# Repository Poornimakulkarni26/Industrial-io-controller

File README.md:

# Industrial IO Controller

A general-purpose industrial I/O controller board built around the **RP2040** microcontroller. Designed for rapid prototyping, hardware validation, and testing across a wide range of sensors, actuators, and communication protocols — all from a single PCB.

## Board Preview

## Features

### Digital I/O
- **20+ configurable digital inputs** — connect buttons, proximity sensors, limit switches, photoelectric sensors, or any industrial-standard digital signal
- **20+ configurable digital outputs** — drive stepper motors, solenoid valves, relays, indicators, and more

### Analog
- **Multi-channel ADC inputs** — for vacuum sensors, pressure transducers, temperature probes, or any 0–3.3V analog signal
- **Current sensing channels** — monitor current draw and detect spikes for motor protection or diagnostics

### Lighting
- **NeoPixel (WS2812B) output** — addressable RGB LED support for status indication, tower lights, or visual feedback

### Storage
- **FRAM (Ferroelectric RAM)** — non-volatile, high-endurance storage for configuration data, counters, or logs that survive power cycles without wear concerns

### Communication Protocols
Designed to test and validate nearly every common protocol from a single board:
- **SPI**
- **I2C**
- **UART**
- **And more** — exposed headers and test points for easy hookup

## Specifications

| Parameter | Value |
|---|---|
| Microcontroller | RP2040 (Dual-core Arm Cortex-M0+, 133 MHz) |
| Digital Inputs | 20+ channels |
| Digital Outputs | 20+ channels |
| Analog Inputs | Multi-channel ADC |
| Current Sensing | Dedicated channels |
| LED Output | NeoPixel (WS2812B) compatible |
| Non-volatile Storage | FRAM |
| Communication | SPI, I2C, UART |
| EDA Tool | KiCad |

## Getting Started

### Viewing the Design
1. Install [KiCad](https://www.kicad.org/) (v7+ recommended)
2. Clone this repository:
   ```bash
   git clone https://github.com/Poornimakulkarni26/Industrial-io-controller.git
   ```
3. Open the `.kicad_pro` project file in KiCad

### Ordering the Board
1. Export Gerber files from KiCad (**File → Fabrication Outputs → Gerbers**)
2. Upload to your preferred PCB manufacturer (JLCPCB, PCBWay etc.)

## Design Highlights

- **Industrial-grade I/O count** — enough channels to prototype full machine control without daisy-chaining expanders
- **Protocol-agnostic test platform** — validate SPI, I2C, UART peripherals without rewiring
- **Mixed-signal capability** — digital I/O, analog sensing, and current monitoring on one board
- **NeoPixel integration** — visual feedback built in, no separate LED driver board needed
- **FRAM over EEPROM** — virtually unlimited write cycles for high-frequency data logging

## Use Cases

- Sensor and actuator validation benches
- Stepper motor driver testing
- Communication protocol bring-up and debugging
- Industrial automation prototyping
- Embedded firmware development and testing

## Author

**Poornima Kulkarni**
Embedded Systems & Industrial Automation Engineer

- GitHub: [@Poornimakulkarni26](https://github.com/Poornimakulkarni26)
https://www.linkedin.com/in/poornima-kulkarni-35ba682a3?utm_source=share_via&utm_content=profile&utm_medium=member_android

## License
This project is open-source under the [MIT License](LICENSE).

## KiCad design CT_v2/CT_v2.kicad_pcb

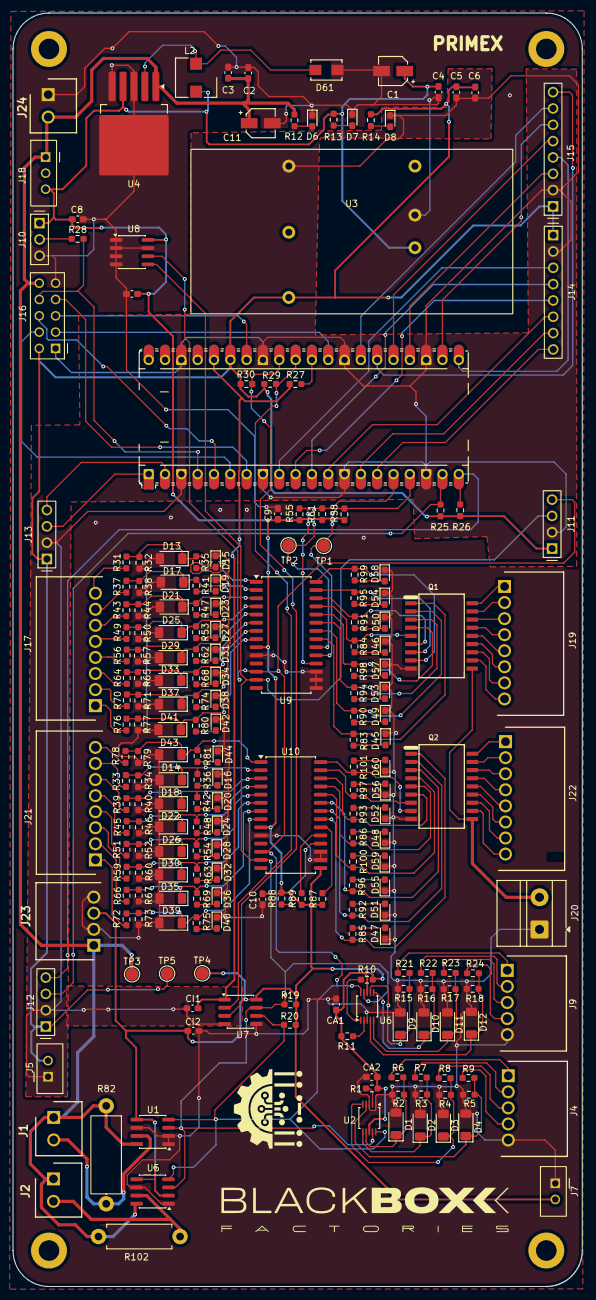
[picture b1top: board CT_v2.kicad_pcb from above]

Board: 4 copper layers, 88.6 x 198.2 mm, 221 parts (0 on the bottom side), 162 nets.

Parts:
100nF3: C_Small; C_0603_1608Metric_Pad1.08x0.95mm_HandSolder
A1: RaspberryPi_Pico; RaspberryPi_Pico_Common_Unspecified
C1: D4L5.5_865060140002; CP_Wurth_WCAP-ASLL-D4L5.5
C2, C4: 100nF; C_0603_1608Metric_Pad1.08x0.95mm_HandSolder
C3: 10pF; C_0603_1608Metric_Pad1.08x0.95mm_HandSolder
C5, C9, C10: 1uF; C_0603_1608Metric_Pad1.08x0.95mm_HandSolder
C6: 10uF; C_0603_1608Metric_Pad1.08x0.95mm_HandSolder
C8: 0.1uF; C_0603_1608Metric_Pad1.08x0.95mm_HandSolder
C11: D4L5.5_865060340001; CP_Wurth_WCAP-ASLL-D4L5.5
CA1, CA2: C_Small; C_0603_1608Metric_Pad1.08x0.95mm_HandSolder
CI1, CI2: C_Small; C_0603_1608Metric_Pad1.08x0.95mm_HandSolder
D1, D2, D3, D4, D9, D10, D11, D12, D13, D14, D17, D18, D21, D22, D25, D26, D29, D30, D33, D35, D37, D39, D41, D43: BZV55C51; D_MiniMELF
D6, D7, D8, D15, D16, D19, D20, D23, D24, D27, D28, D31, D32, D34, D36, D38, D40, D42, D44, D45, D46, D47, D48, D49, D50, D51, D52, D53, D54, D55, D56, D57, D58, D59, D60: LED; LED_0603_1608Metric_Pad1.05x0.95mm_HandSolder
D61: M7; M7_DIO
H1, H2, H3, H4: MountingHole; MountingHole_3.2mm_M3_DIN965_Pad
J1, J2, J24: 691321100002; SHDR2W80P0X350_1X2_840X720X920P
J4, J9: 691382010005; SHDRRA5W80P0X250_1X5_1450X1010X830P
J5, J7: 68800211622; J_Wurth_WR-WTB_68800211622
J10: 61300311121; J_Wurth_WR-PHD_61300311121
J11, J12, J13: 61000418221; J_Wurth_WR-PHD_61300411121
J14, J15: 61000821121; J_Wurth_WR-PHD_61300811121
J16: 61301021821; J_Wurth_WR-PHD_61301021821
J17, J19, J21, J22: 691382010008; SHDRRA8W80P0X250_1X8_2200X1010X830P
J18: 68800311622; J_Wurth_WR-WTB_68800311622
J20: Screw_Terminal_01x02; TerminalBlock_MetzConnect_Type011_RT05502HBLC_1x02_P5.00mm_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
J23: 691382010004; SHDRRA4W80P0X250_1X4_1200X1010X810P
L2: 6033R_744778520; L_Wurth_WE-PD-6033R
Q1, Q2: TBD62083AFG_EL; SOIC127P1030X245-18N
R1, R19, R20, R25, R26, R27, R29, R30, R55, R58, R61, R87, R88, R89: 10k; R_0603_1608Metric_Pad0.98x0.95mm_HandSolder
R2, R3, R4, R5, R15, R16, R17, R18, R32, R34, R38, R40, R44, R46, R50, R52, R57, R60, R65, R67, R71, R73, R77, R79: 1k; R_0603_1608Metric_Pad0.98x0.95mm_HandSolder
R6, R7, R8, R9, R21, R22, R23, R24: 2k; R_0603_1608Metric_Pad0.98x0.95mm_HandSolder
R10, R11: 10K; R_0603_1608Metric_Pad0.98x0.95mm_HandSolder
R12, R13, R14: 1.2k; R_0603_1608Metric_Pad0.98x0.95mm_HandSolder
R28: 470; R_0603_1608Metric_Pad0.98x0.95mm_HandSolder
R31, R33, R37, R39, R43, R45, R49, R51, R56, R59, R64, R66, R70, R72, R76, R78: 3.9k; R_0603_1608Metric_Pad0.98x0.95mm_HandSolder
R35, R36, R41, R42, R47, R48, R53, R54, R62, R63, R68, R69, R74, R75, R80, R81, R83, R84, R85, R86, R90, R91, R92, R93, R94, R95, R96, R97, R98, R99, R100, R101: 330; R_0603_1608Metric_Pad0.98x0.95mm_HandSolder
R82: 0.1; R_Axial_DIN0414_L11.9mm_D4.5mm_P15.24mm_Horizontal
R102: 0.1; R_Axial_DIN0411_L9.9mm_D3.6mm_P12.70mm_Horizontal
TP1, TP2, TP3, TP4, TP5: TestPoint; TestPoint_Pad_D2.0mm
U1, U5: INA219AxD; SOIC-8_3.9x4.9mm_P1.27mm
U2, U6: ADS1115IDGS; TSSOP-10_3x3mm_P0.5mm
U3: ECB4U-05S03; Ec4ub-24s05
U4: LM2576HVS-5; TO-263-5_TabPin3
U7: ISO1540; SOIC-8_3.9x4.9mm_P1.27mm
U8: FM24C64B; SOIC-8_3.9x4.9mm_P1.27mm
U9: IN_MCP23017; SOIC-28W_7.5x17.9mm_P1.27mm
U10: MCP23017_SO; SOIC-28W_7.5x17.9mm_P1.27mm

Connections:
+3.3V: A1.35 (ADC_VREF), C5.1, C6.1, J5.2, J11.1, J12.1, J13.1, J14.1, J15.1, J16.2, R14.1, R25.1, R26.2, R29.1, R30.2, TP5.1, U3.3 (+V)
+5V: 100nF3.1, C1.1, C4.1, C8.1, C9.1, C10.1, CA1.1, CA2.1, CI2.2, J7.2, J10.1, J18.3, J23.3, L2.2, R1.1, R10.1, R11.1, R13.1, R19.1, R20.2, R55.2, R58.1, R61.1, R87.1, R88.2, R89.1, TP4.1, U1.5 (VS), U2.8 (VDD), U3.1 (IN+), U4.4 (FB), U5.2 (A0), U5.5 (VS), U6.8 (VDD), U7.8 (VCC2), U8.8 (VDD), U9.9 (VDD), U10.9 (VDD), U10.15 (A0)
+24V: C2.1, C3.1, C11.1, J1.1, J2.1, J16.10, J18.1, J23.1, J24.2, R12.1, R82.1, R102.1, TP3.1, U1.8 (IN+), U4.1 (VIN), U5.8 (IN+)
+ 3.3V: A1.36 (3V3), CI1.1, R27.1, U7.1 (VCC1)
-24VA: J1.2, R82.2, U1.7 (IN-)
-24VB: J2.2, R102.2, U5.7 (IN-)
ADC2: A1.34 (GPIO28_ADC2), J16.5
CS1: A1.12 (GPIO9), J14.6
CS2: A1.14 (GPIO10), J14.7
CS3: A1.15 (GPIO11), J14.8
Din: A1.4 (GPIO2), J16.8, R28.2
GND: 100nF3.2, C1.2, C2.2, C3.2, C4.2, C8.2, C9.2, C10.2, C11.2, CA1.2, CA2.2, CI2.1, D1.2 (A), D2.2 (A), D3.2 (A), D4.2 (A), D6.1 (K), D7.1 (K), D9.2 (A), D10.2 (A), D11.2 (A), D12.2 (A), D13.2 (A), D14.2 (A), D15.1 (K), D16.1 (K), D17.2 (A), D18.2 (A), D19.1 (K), D20.1 (K), D21.2 (A), D22.2 (A), D23.1 (K), D24.1 (K), D25.2 (A), D26.2 (A), D27.1 (K), D28.1 (K), D29.2 (A), D30.2 (A), D31.1 (K), D32.1 (K), D33.2 (A), D34.1 (K), D35.2 (A), D36.1 (K), D37.2 (A), D38.1 (K), D39.2 (A), D40.1 (K), D41.2 (A), D42.1 (K), D43.2 (A), D44.1 (K), D45.1 (K), D46.1 (K), D47.1 (K), D48.1 (K), D49.1 (K), D50.1 (K), D51.1 (K), D52.1 (K), D53.1 (K), D54.1 (K), D55.1 (K), D56.1 (K), D57.1 (K), D58.1 (K), D59.1 (K), D60.1 (K), D61.1, J4.5, J7.1, J9.5, J10.3, J16.9, J20.1, J23.2, J23.4, J24.1, Q1.9 (GND), Q2.9 (GND), R2.2, R3.2, R4.2, R5.2, R15.2, R16.2, R17.2, R18.2, R32.2, R34.2, R38.2, R40.2, R44.2, R46.2, R50.2, R52.2, R57.2, R60.2, R65.2, R67.2, R71.2, R73.2, R77.2, R79.2, U1.1 (A1), U1.2 (A0), U1.6 (GND), U2.1 (ADDR), U2.3 (GND), U3.2 (IN-), U4.3 (GND), U4.5 (~ON/OFF), U5.1 (A1), U5.6 (GND), U6.3 (GND), U7.5 (GND2), U8.1 (A0), U8.2 (A1), U8.3 (A2), U8.4 (VSS), U8.7 (WP), U9.10 (VSS), U9.15 (A0), U9.16 (A1), U9.17 (A2), U10.10 (VSS), U10.16 (A1), U10.17 (A2)
GP3: A1.5 (GPIO3), J16.6
GP4: A1.6 (GPIO4), J16.4
GP5: A1.7 (GPIO5), J16.7
GP22: A1.29 (GPIO22), J16.3
IP1: J17.8, R31.1
IP1M: D13.1 (K), R31.2, R32.1, R35.1, U9.1 (GPB0)
IP2: J17.7, R37.1
IP2M: D17.1 (K), R37.2, R38.1, R41.1, U9.2 (GPB1)
IP3: J17.6, R43.1
IP3M: D21.1 (K), R43.2, R44.1, R47.1, U9.3 (GPB2)
IP4: J17.5, R49.1
IP4M: D25.1 (K), R49.2, R50.1, R53.1, U9.4 (GPB3)
IP5: J17.4, R56.1
IP5M: D29.1 (K), R56.2, R57.1, R62.1, U9.5 (GPB4)
IP6: J17.3, R64.1
IP6M: D33.1 (K), R64.2, R65.1, R68.1, U9.6 (GPB5)
IP7: J17.2, R70.1
IP7M: D37.1 (K), R70.2, R71.1, R74.1, U9.7 (GPB6)
IP8: J17.1, R76.1
IP8M: D41.1 (K), R76.2, R77.1, R80.1, U9.8 (GPB7)
IP9: J21.8, R78.1
IP9M: D43.1 (K), R78.2, R79.1, R81.1, U10.1 (GPB0)
IP10: J21.7, R33.1
IP10M: D14.1 (K), R33.2, R34.1, R36.1, U10.2 (GPB1)
IP11: J21.6, R39.1
IP11M: D18.1 (K), R39.2, R40.1, R42.1, U10.3 (GPB2)
IP12: J21.5, R45.1
IP12M: D22.1 (K), R45.2, R46.1, R48.1, U10.4 (GPB3)
IP13: J21.4, R51.1
IP13M: D26.1 (K), R51.2, R52.1, R54.1, U10.5 (GPB4)
IP14: J21.3, R59.1
IP14M: D30.1 (K), R59.2, R60.1, R63.1, U10.6 (GPB5)
IP15: J21.2, R66.1
IP15M: D35.1 (K), R66.2, R67.1, R69.1, U10.7 (GPB6)
IP16: J21.1, R72.1
IP16M: D39.1 (K), R72.2, R73.1, R75.1, U10.8 (GPB7)
I_GND: A1.3 (GND), A1.8 (GND), A1.13 (GND), A1.18 (GND), A1.23 (GND), A1.28 (GND), A1.33 (AGND), A1.38 (GND), C5.2, C6.2, CI1.2, D8.1 (K), J5.1, J11.2, J12.2, J13.2, J14.2, J15.2, J16.1, U3.5 (-V), U7.4 (GND1)
I_SCL: A1.32 (GPIO27_ADC1), R30.1, U7.3 (SCL1)
I_SDA: A1.31 (GPIO26_ADC0), R29.2, U7.2 (SDA1)
MISO: A1.11 (GPIO8), J14.4
MOSI: A1.10 (GPIO7), J14.5
unnamed: A1.30 (RUN), R27.2
unnamed: D1.1 (K), R2.1, R6.2, U2.7 (AIN3)
unnamed: D2.1 (K), R3.1, R7.2, U2.6 (AIN2)
unnamed: D3.1 (K), R4.1, R8.2, U2.5 (AIN1)
unnamed: D4.1 (K), R5.1, R9.2, U2.4 (AIN0)
unnamed: D6.2 (A), R12.2
unnamed: D7.2 (A), R13.2
unnamed: D8.2 (A), R14.2
unnamed: D9.1 (K), R15.1, R21.2, U6.7 (AIN3)
unnamed: D10.1 (K), R16.1, R22.2, U6.6 (AIN2)
unnamed: D11.1 (K), R17.1, R23.2, U6.5 (AIN1)
unnamed: D12.1 (K), R18.1, R24.2, U6.4 (AIN0)
unnamed: D15.2 (A), R35.2
unnamed: D16.2 (A), R36.2
unnamed: D19.2 (A), R41.2
unnamed: D20.2 (A), R42.2
unnamed: D23.2 (A), R47.2
unnamed: D24.2 (A), R48.2
unnamed: D27.2 (A), R53.2
unnamed: D28.2 (A), R54.2
unnamed: D31.2 (A), R62.2
unnamed: D32.2 (A), R63.2
unnamed: D34.2 (A), R68.2
unnamed: D36.2 (A), R69.2
unnamed: D38.2 (A), R74.2
unnamed: D40.2 (A), R75.2
unnamed: D42.2 (A), R80.2
unnamed: D44.2 (A), R81.2
unnamed: D45.2 (A), R83.2
unnamed: D46.2 (A), R84.2
unnamed: D47.2 (A), R85.2
unnamed: D48.2 (A), R86.2
unnamed: D49.2 (A), R90.2
unnamed: D50.2 (A), R91.2
unnamed: D51.2 (A), R92.2
unnamed: D52.2 (A), R93.2
unnamed: D53.2 (A), R94.2
unnamed: D54.2 (A), R95.2
unnamed: D55.2 (A), R96.2
unnamed: D56.2 (A), R97.2
unnamed: D57.2 (A), R98.2
unnamed: D58.2 (A), R99.2
unnamed: D59.2 (A), R100.2
unnamed: D60.2 (A), R101.2
unnamed: J4.1, R6.1
unnamed: J4.2, R7.1
unnamed: J4.3, R8.1
unnamed: J4.4, R9.1
unnamed: J9.1, R21.1
unnamed: J9.2, R22.1
unnamed: J9.3, R23.1
unnamed: J9.4, R24.1
unnamed: J10.2, R28.1
unnamed: J19.1, Q1.18 (O1)
unnamed: J19.2, Q1.17 (O2)
unnamed: J19.3, Q1.16 (O3)
unnamed: J19.4, Q1.15 (O4)
unnamed: J19.5, Q1.14 (O5)
unnamed: J19.6, Q1.13 (O6)
unnamed: J19.7, Q1.12 (O7)
unnamed: J19.8, Q1.11 (O8)
unnamed: J22.1, Q2.18 (O1)
unnamed: J22.2, Q2.17 (O2)
unnamed: J22.3, Q2.16 (O3)
unnamed: J22.4, Q2.15 (O4)
unnamed: J22.5, Q2.14 (O5)
unnamed: J22.6, Q2.13 (O6)
unnamed: J22.7, Q2.12 (O7)
unnamed: J22.8, Q2.11 (O8)
unnamed: R1.2, U2.2 (ALERT/RDY)
unnamed: D61.2, L2.1, U4.2 (OUT)
unnamed: R10.2, U6.1 (ADDR)
unnamed: R11.2, U6.2 (ALERT/RDY)
OP1: Q1.1 (I1), R83.1, U9.21 (GPA0)
OP2: Q1.2 (I2), R90.1, U9.22 (GPA1)
OP3: Q1.3 (I3), R94.1, U9.23 (GPA2)
OP4: Q1.4 (I4), R98.1, U9.24 (GPA3)
OP5: Q1.5 (I5), R84.1, U9.25 (GPA4)
OP6: Q1.6 (I6), R91.1, U9.26 (GPA5)
OP7: Q1.7 (I7), R95.1, U9.27 (GPA6)
OP8: Q1.8 (I8), R99.1, U9.28 (GPA7)
OP9: Q2.1 (I1), R85.1, U10.21 (GPA0)
OP10: Q2.2 (I2), R92.1, U10.22 (GPA1)
OP11: Q2.3 (I3), R96.1, U10.23 (GPA2)
OP12: Q2.4 (I4), R100.1, U10.24 (GPA3)
OP13: Q2.5 (I5), R86.1, U10.25 (GPA4)
OP14: Q2.6 (I6), R93.1, U10.26 (GPA5)
OP15: Q2.7 (I7), R97.1, U10.27 (GPA6)
OP16: Q2.8 (I8), R101.1, U10.28 (GPA7)
RST: R55.1, U9.18 (~RESET)
RST1: R88.1, U10.18 (~RESET)
Rx: A1.2 (GPIO1), J13.4
SCK: A1.9 (GPIO6), J14.3
SCL: J11.4, R20.1, U1.4 (SCL), U2.10 (SCL), U5.4 (SCL), U6.10 (SCL), U7.6 (SCL2), U8.6 (SCL), U9.12 (SCK), U10.12 (SCK)
SCL2: A1.20 (GPIO15), J12.4, R26.1
SDA: J11.3, R19.2, U1.3 (SDA), U2.9 (SDA), U5.3 (SDA), U6.9 (SDA), U7.7 (SDA2), U8.5 (SDA), U9.13 (SDA), U10.13 (SDA)
SDA2: A1.19 (GPIO14), J12.3, R25.2
Tx: A1.1 (GPIO0), J13.3
Volt: J20.2, Q1.10 (COMMON), Q2.10 (COMMON)
WCS: A1.22 (GPIO17), J15.6
WINT: A1.26 (GPIO20), J15.8
WMISO: A1.21 (GPIO16), J15.4
WMOSI: A1.25 (GPIO19), J15.5
WRST: A1.27 (GPIO21), J15.7
WSCLK: A1.24 (GPIO18), J15.3
intA: A1.16 (GPIO12), R61.2, TP2.1, U9.20 (INTA)
intA1: R87.2, U10.20 (INTA)
intB: A1.17 (GPIO13), R58.2, TP1.1, U9.19 (INTB)
intB1: R89.2, U10.19 (INTB)

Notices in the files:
README.md:
License: MIT
